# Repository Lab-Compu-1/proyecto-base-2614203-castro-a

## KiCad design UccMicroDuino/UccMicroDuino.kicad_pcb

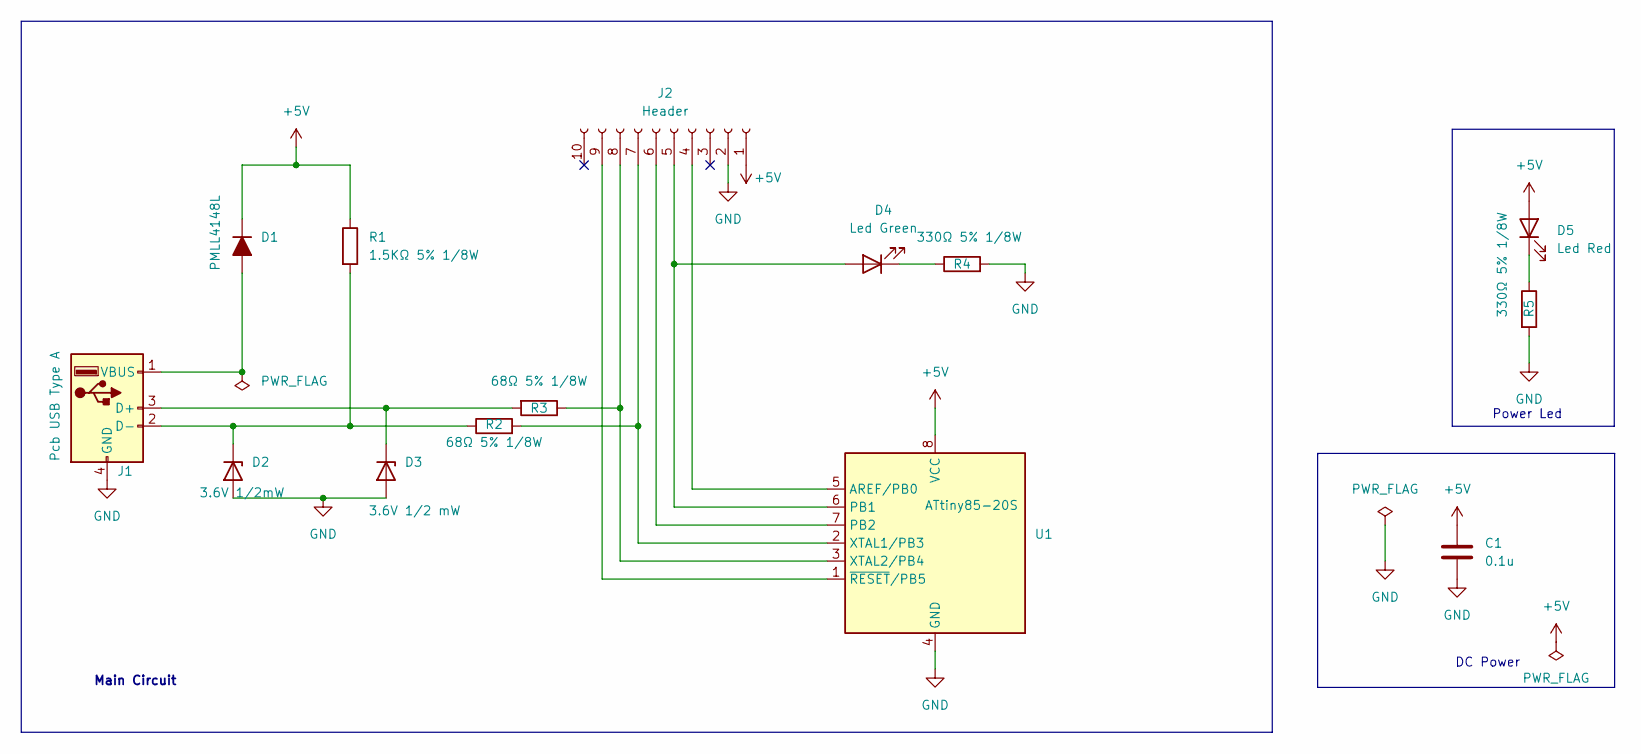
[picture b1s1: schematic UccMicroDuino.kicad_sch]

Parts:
C1: 0.1u; C_0805_2012Metric_Pad1.18x1.45mm_HandSolder
D1: PMLL4148L; D_MiniMELF
D2: 3.6V 1/2mW; D_SOD-123
D3: 3.6V 1/2 mW; D_SOD-123
D4: Led Green; ledSMD
D5: Led Red; ledSMD
J1: Pcb USB Type A; USB_A_UCC
J2: Header; PinHeader_1x10_P2.54mm_Vertical
R1: 1.5KΩ 5% 1/8W; R_0805_2012Metric_Pad1.20x1.40mm_HandSolder
R2, R3: 68Ω 5% 1/8W; R_0805_2012Metric_Pad1.20x1.40mm_HandSolder
R4, R5: 330Ω 5% 1/8W; R_0805_2012Metric_Pad1.20x1.40mm_HandSolder
U1: ATtiny85-20S; SOIC-8_5.3x5.3mm_P1.27mm

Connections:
+5V: C1.1, D1.1 (K), D5.2 (A), J2.1, R1.1, U1.8 (VCC)
GND: C1.2, D2.2 (A), D3.2 (A), J1.4 (GND), J2.2, R4.2, R5.2, U1.4 (GND)
unnamed: D1.2 (A), J1.1 (VBUS)
unnamed: D2.1 (K), J1.2 (D-), R1.2, R2.1
unnamed: D3.1 (K), J1.3 (D+), R3.2
unnamed: D4.2 (A), J2.5, U1.6 (PB1)
unnamed: D4.1 (K), R4.1
unnamed: D5.1 (K), R5.1
unnamed: J2.4, U1.5 (AREF/PB0)
unnamed: J2.6, U1.7 (PB2)
unnamed: J2.7, R2.2, U1.2 (XTAL1/PB3)
unnamed: J2.8, R3.1, U1.3 (XTAL2/PB4)
unnamed: J2.9, U1.1 (~RESET/PB5)

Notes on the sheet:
Power Led
Main Circuit
DC Power

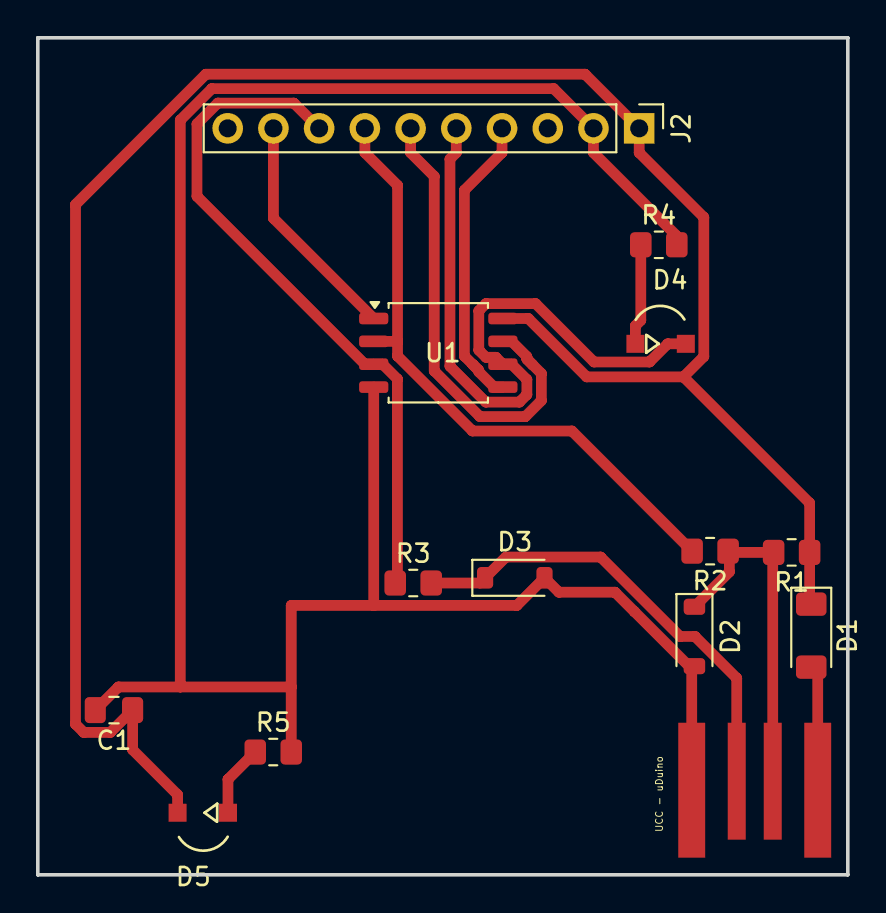
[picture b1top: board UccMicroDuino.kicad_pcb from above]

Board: 2 copper layers, 45.0 x 46.5 mm, 14 parts (0 on the bottom side), 13 nets.

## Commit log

2026-03-30 GitHub Classroom Feedback
2026-03-30 Setting up GitHub Classroom Feedback
2026-05-18 Trabajo final
2026-05-18 modificacion simple
2026-05-18 2614203 primer versionado con git Bash
